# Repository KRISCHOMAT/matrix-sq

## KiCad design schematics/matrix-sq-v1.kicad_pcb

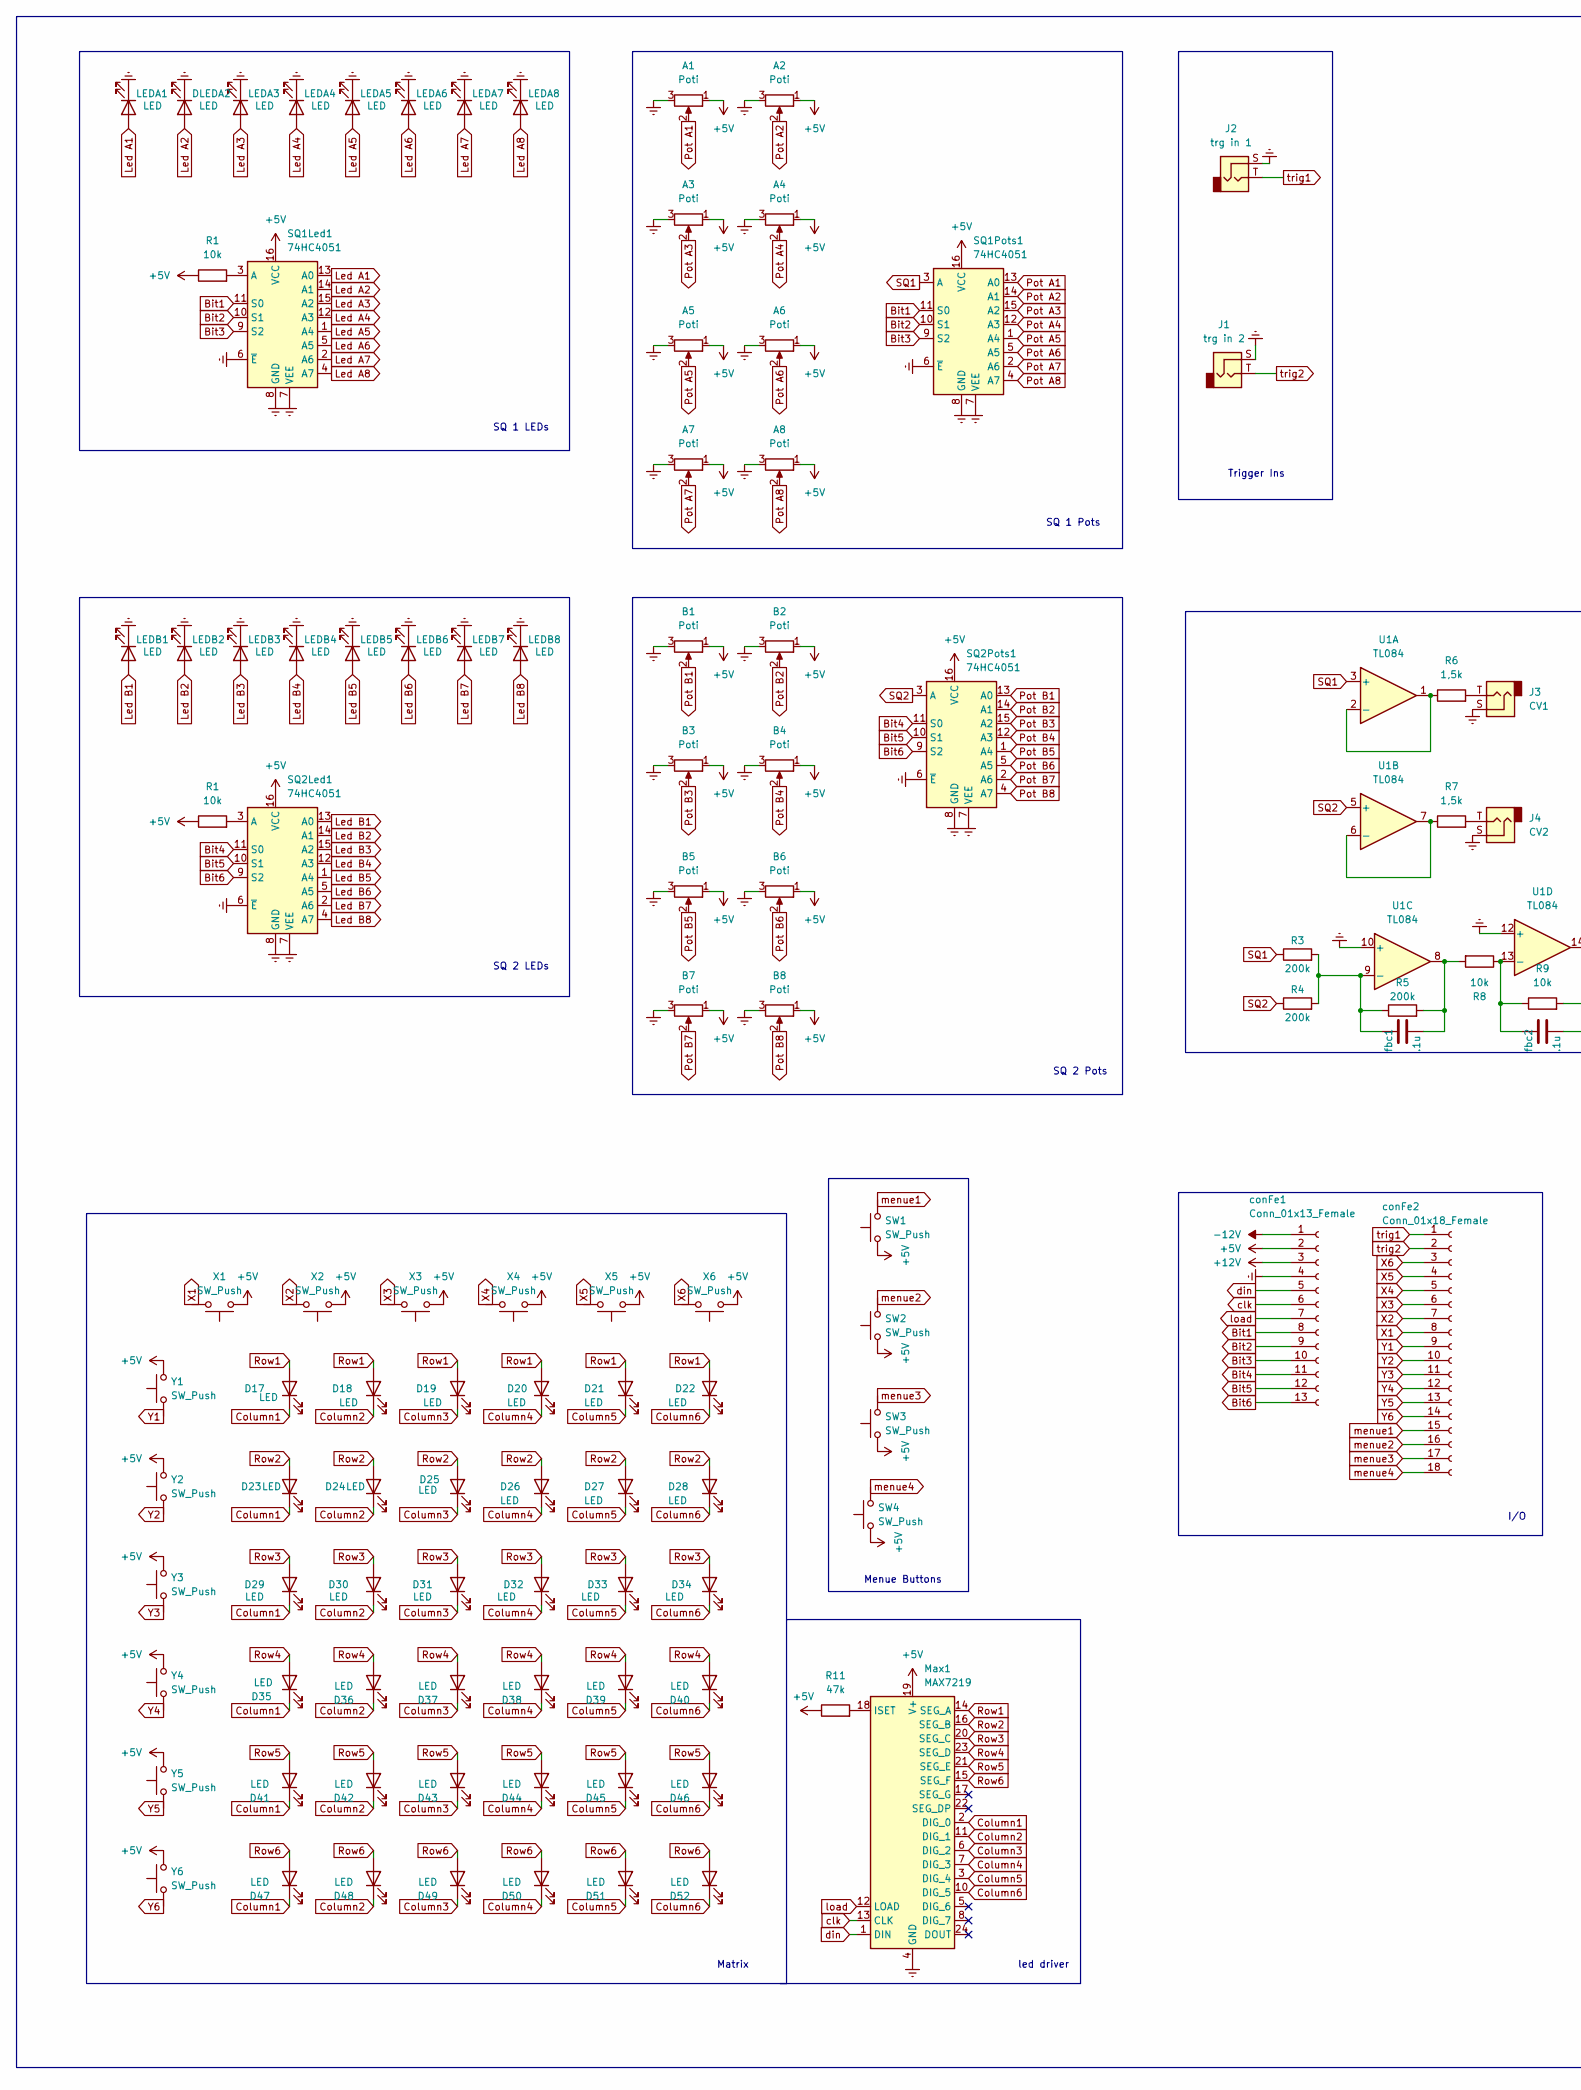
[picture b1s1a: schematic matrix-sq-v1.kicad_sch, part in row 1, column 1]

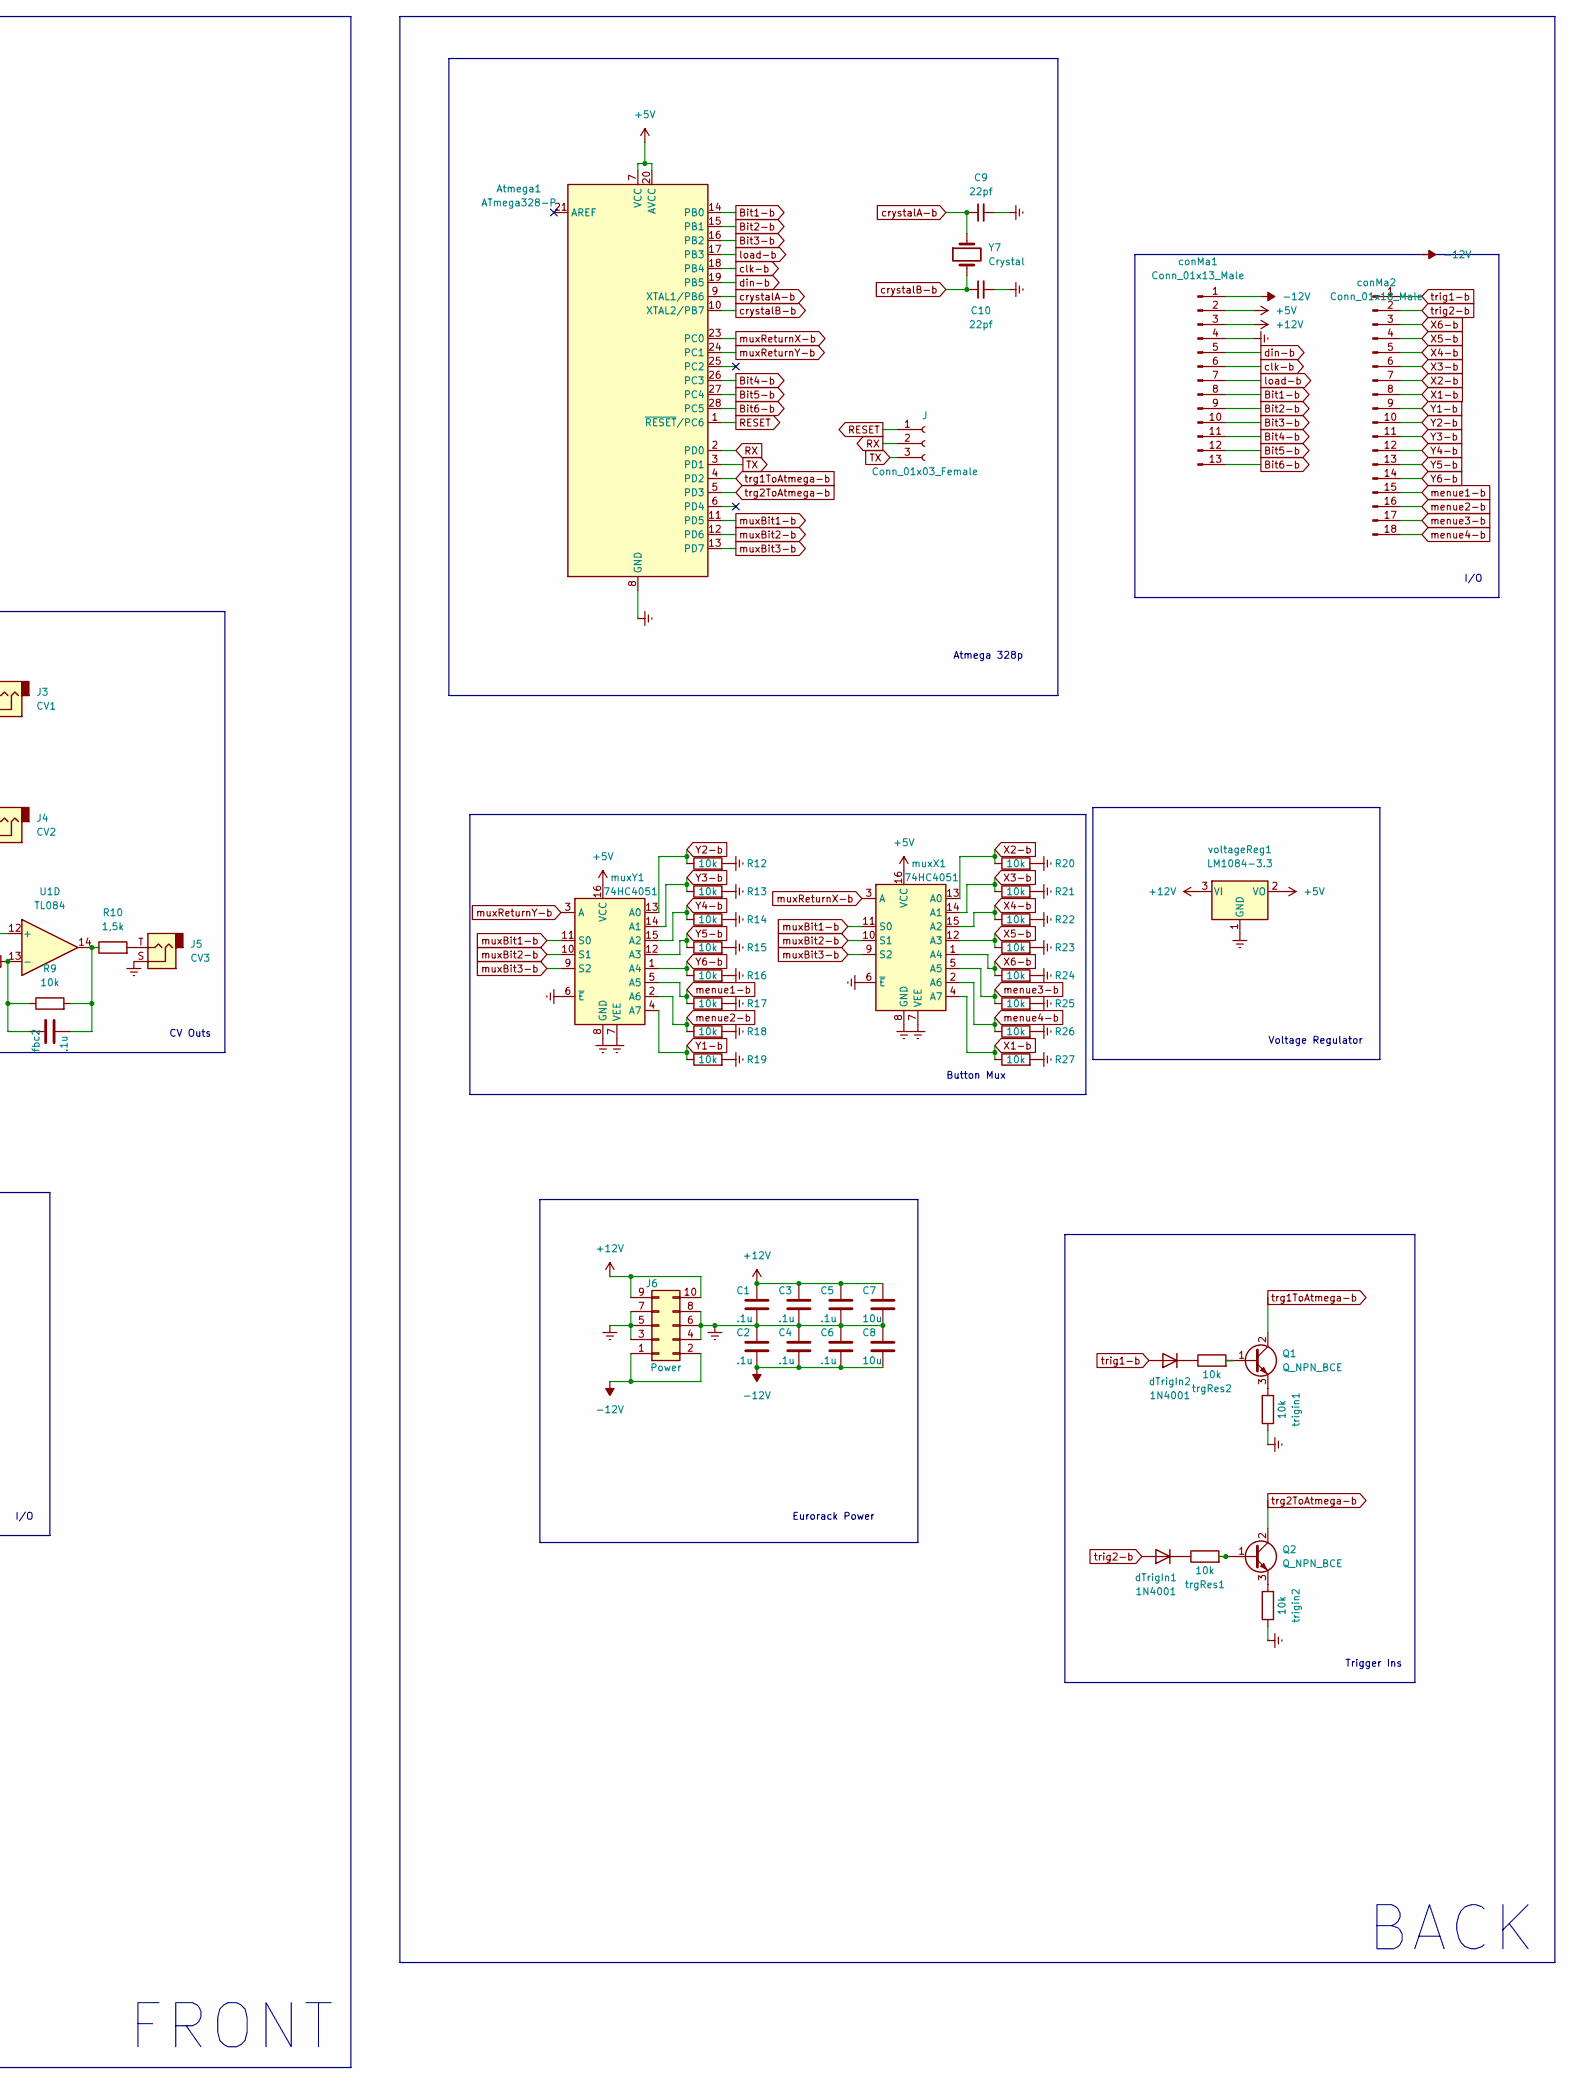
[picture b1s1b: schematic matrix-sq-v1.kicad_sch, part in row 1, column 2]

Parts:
A1, A2, A3, A4, A5, A6, A7, A8: Poti; Potentiometer_Alpha_RD901F-40-00D_Single_Vertical
Atmega1: ATmega328-P; DIP-28_W7.62mm
B1, B2, B3, B4, B5, B6, B7, B8: Poti; Potentiometer_Alpha_RD901F-40-00D_Single_Vertical
C1, C2, C3, C4, C5, C6: .1u; C_Disc_D3.0mm_W1.6mm_P2.50mm
C7, C8: 10u; C_Disc_D3.0mm_W1.6mm_P2.50mm
C9, C10: 22pf; C_Disc_D3.0mm_W1.6mm_P2.50mm
D17, D18, D19, D20, D21, D22, D23, D24, D25, D26, D27, D28, D29, D30, D31, D32, D33, D34, D35, D36, D37, D38, D39, D40, D41, D42, D43, D44, D45, D46, D47, D48, D49, D50, D51, D52: LED; LED_D3.0mm
DLEDA2: LED; LED_D3.0mm
J: Conn_01x03_Female; PinHeader_1x03_P2.54mm_Vertical
J1: trg in 2; Jack_3.5mm_QingPu_WQP-PJ398SM_Vertical_CircularHoles
J2: trg in 1; Jack_3.5mm_QingPu_WQP-PJ398SM_Vertical_CircularHoles
J3: CV1; Jack_3.5mm_QingPu_WQP-PJ398SM_Vertical_CircularHoles
J4: CV2; Jack_3.5mm_QingPu_WQP-PJ398SM_Vertical_CircularHoles
J5: CV3; Jack_3.5mm_QingPu_WQP-PJ398SM_Vertical_CircularHoles
J6: Power; PinHeader_2x05_P2.54mm_Vertical
LEDA1, LEDA3, LEDA4, LEDA5, LEDA6, LEDA7, LEDA8: LED; LED_D3.0mm
LEDB1, LEDB2, LEDB3, LEDB4, LEDB5, LEDB6, LEDB7, LEDB8: LED; LED_D3.0mm
Max1: MAX7219; DIP-24_W7.62mm
Q1, Q2: Q_NPN_BCE; TO-92Flat
R1, R12: R600; R_Axial_DIN0207_L6.3mm_D2.5mm_P7.62mm_Horizontal
R3, R4, R5: 200k; R_Axial_DIN0207_L6.3mm_D2.5mm_P7.62mm_Horizontal
R6, R7, R10: 1,5k; R_Axial_DIN0207_L6.3mm_D2.5mm_P7.62mm_Horizontal
R8, R9, R13, R14, R15, R16, R17, R18, R19, R20, R21, R22, R23, R24, R25, R26, R27: 10k; R_Axial_DIN0207_L6.3mm_D2.5mm_P7.62mm_Horizontal
R11: 47k; R_Axial_DIN0207_L6.3mm_D2.5mm_P7.62mm_Horizontal
SQ1Led1, SQ1Pots1, SQ2Led1, SQ2Pots1: 74HC4051; DIP-16_W7.62mm_Socket
SW1, SW2, SW3, SW4: SW_Push; push_button
U1: TL084; DIP-14_W7.62mm_Socket
X1, X2, X3, X4, X5, X6: SW_Push; push_button
Y1, Y2, Y3, Y4, Y5, Y6: SW_Push; push_button
Y7: Crystal; Crystal_HC18-U_Vertical
conFe1: Conn_01x13_Female; PinHeader_1x13_P2.54mm_Vertical
conFe2: Conn_01x18_Female; PinHeader_1x18_P2.54mm_Vertical
conMa1: Conn_01x13_Male; PinHeader_1x13_P2.54mm_Vertical
conMa2: Conn_01x18_Male; PinSocket_1x18_P2.54mm_Vertical
dTrigIn1, dTrigIn2: 1N4001; D_DO-41_SOD81_P10.16mm_Horizontal
fbc1, fbc2: .1u; C_Disc_D3.0mm_W1.6mm_P2.50mm
muxX1: 74HC4051; DIP-16_W7.62mm_Socket
muxY1: 74HC4051; DIP-16_W7.62mm_Socket
trgRes1, trgRes2: 10k; R_Axial_DIN0207_L6.3mm_D2.5mm_P7.62mm_Horizontal
trigin1, trigin2: 10k; R_Axial_DIN0207_L6.3mm_D2.5mm_P7.62mm_Horizontal
voltageReg1: LM1084-3.3; TO-220-3_Vertical

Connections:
+5V: A1.1, A2.1, A3.1, A4.1, A5.1, A6.1, A7.1, A8.1, Atmega1.7 (VCC), Atmega1.20 (AVCC), B1.1, B2.1, B3.1, B4.1, B5.1, B6.1, B7.1, B8.1, Max1.19 (V+), R1.1, R11.1, SQ1Led1.16 (VCC), SQ1Pots1.16 (VCC), SQ2Led1.16 (VCC), SQ2Pots1.16 (VCC), SW1.1, SW2.1, SW3.1, SW4.1, X1.1, X2.1, X3.1, X4.1, X5.1, X6.1, Y1.2, Y2.2, Y3.2, Y4.2, Y5.2, Y6.2, conFe1.2, conMa1.2, muxX1.16 (VCC), muxY1.16 (VCC), voltageReg1.2 (VO); also elsewhere on the board
+12V: C1.1, C3.1, C5.1, C7.1, J6.9, J6.10, conFe1.3, conMa1.3, voltageReg1.3 (VI)
-12V: C2.2, C4.2, C6.2, C8.2, J6.1, J6.2, conFe1.1, conMa1.1
Bit1: SQ1Led1.11 (S0), SQ1Pots1.11 (S0), conFe1.8
Bit1-b: Atmega1.14 (PB0), conMa1.8
Bit2: SQ1Led1.10 (S1), SQ1Pots1.10 (S1), conFe1.9
Bit2-b: Atmega1.15 (PB1), conMa1.9
Bit3: SQ1Led1.9 (S2), SQ1Pots1.9 (S2), conFe1.10
Bit3-b: Atmega1.16 (PB2), conMa1.10
Bit4: SQ2Led1.11 (S0), SQ2Pots1.11 (S0), conFe1.11
Bit4-b: Atmega1.26 (PC3), conMa1.11
Bit5: SQ2Led1.10 (S1), SQ2Pots1.10 (S1), conFe1.12
Bit5-b: Atmega1.27 (PC4), conMa1.12
Bit6: SQ2Led1.9 (S2), SQ2Pots1.9 (S2), conFe1.13
Bit6-b: Atmega1.28 (PC5), conMa1.13
Column1: D17.1 (K), D23.1 (K), D29.1 (K), D35.1 (K), D41.1 (K), D47.1 (K), Max1.2 (DIG_0)
Column2: D18.1 (K), D24.1 (K), D30.1 (K), D36.1 (K), D42.1 (K), D48.1 (K), Max1.11 (DIG_1)
Column3: D19.1 (K), D25.1 (K), D31.1 (K), D37.1 (K), D43.1 (K), D49.1 (K), Max1.6 (DIG_2)
Column4: D20.1 (K), D26.1 (K), D32.1 (K), D38.1 (K), D44.1 (K), D50.1 (K), Max1.7 (DIG_3)
Column5: D21.1 (K), D27.1 (K), D33.1 (K), D39.1 (K), D45.1 (K), D51.1 (K), Max1.3 (DIG_4)
Column6: D22.1 (K), D28.1 (K), D34.1 (K), D40.1 (K), D46.1 (K), D52.1 (K), Max1.10 (DIG_5)
Earth: A1.3, A2.3, A3.3, A4.3, A5.3, A6.3, A7.3, A8.3, Atmega1.8 (GND), Atmega1.22 (GND), B1.3, B2.3, B3.3, B4.3, B5.3, B6.3, B7.3, B8.3, C1.2, C2.1, C3.2, C4.1, C5.2, C6.1, C7.2, C8.1, C9.2, C10.2, DLEDA2.1 (K), J1.S, J2.S, J3.S, J4.S, J5.S, J6.3, J6.4, J6.5, J6.6, J6.7, J6.8, LEDA1.1 (K), LEDA3.1 (K), LEDA4.1 (K), LEDA5.1 (K), LEDA6.1 (K), LEDA7.1 (K), LEDA8.1 (K), LEDB1.1 (K), LEDB2.1 (K), LEDB3.1 (K), LEDB4.1 (K), LEDB5.1 (K), LEDB6.1 (K), LEDB7.1 (K), LEDB8.1 (K), Max1.4 (GND), Max1.9 (GND), R12.2, R13.2, R14.2, R15.2, R16.2, R17.2, R18.2, R19.2, R20.2, R21.2, R22.2, R23.2, R24.2, R25.2, R26.2, R27.2, SQ1Led1.6 (~E), SQ1Led1.7 (VEE), SQ1Led1.8 (GND), SQ1Pots1.6 (~E), SQ1Pots1.7 (VEE), SQ1Pots1.8 (GND), SQ2Led1.6 (~E), SQ2Led1.7 (VEE), SQ2Led1.8 (GND), SQ2Pots1.6 (~E), SQ2Pots1.7 (VEE), SQ2Pots1.8 (GND), U1.10 (+), U1.12 (+), conFe1.4, conMa1.4, muxX1.6 (~E), muxX1.7 (VEE), muxX1.8 (GND), muxY1.6 (~E), muxY1.7 (VEE), muxY1.8 (GND), trigin1.1, trigin2.1, voltageReg1.1 (GND)
Led A1: LEDA1.2 (A), SQ1Led1.13 (A0)
Led A2: DLEDA2.2 (A), SQ1Led1.14 (A1)
Led A3: LEDA3.2 (A), SQ1Led1.15 (A2)
Led A4: LEDA4.2 (A), SQ1Led1.12 (A3)
Led A5: LEDA5.2 (A), SQ1Led1.1 (A4)
Led A6: LEDA6.2 (A), SQ1Led1.5 (A5)
Led A7: LEDA7.2 (A), SQ1Led1.2 (A6)
Led A8: LEDA8.2 (A), SQ1Led1.4 (A7)
Led B1: LEDB1.2 (A), SQ2Led1.13 (A0)
Led B2: LEDB2.2 (A), SQ2Led1.14 (A1)
Led B3: LEDB3.2 (A), SQ2Led1.15 (A2)
Led B4: LEDB4.2 (A), SQ2Led1.12 (A3)
Led B5: LEDB5.2 (A), SQ2Led1.1 (A4)
Led B6: LEDB6.2 (A), SQ2Led1.5 (A5)
Led B7: LEDB7.2 (A), SQ2Led1.2 (A6)
Led B8: LEDB8.2 (A), SQ2Led1.4 (A7)
unnamed: J3.T, R6.2
unnamed: J4.T, R7.2
unnamed: J5.T, R10.2
unnamed 41: Max1.18 (ISET), R11.2; also elsewhere on the board
unnamed: Q1.1 (B), trgRes2.2
unnamed: Q1.3 (E), trigin1.2
unnamed: Q2.1 (B), trgRes1.2
unnamed: Q2.3 (E), trigin2.2
unnamed: R3.2, R4.2, R5.1, U1.9 (-), fbc1.1
unnamed: R5.2, R8.2, U1.8, fbc1.2
unnamed: R6.1, U1.1, U1.2 (-)
unnamed: R7.1, U1.6 (-), U1.7
unnamed: R8.1, R9.1, U1.13 (-), fbc2.1
unnamed: R9.2, R10.1, U1.14, fbc2.2
unnamed: dTrigIn1.1 (K), trgRes1.1
unnamed: dTrigIn2.1 (K), trgRes2.1
Pot A1: A1.2, SQ1Pots1.13 (A0)
Pot A2: A2.2, SQ1Pots1.14 (A1)
Pot A3: A3.2, SQ1Pots1.15 (A2)
Pot A4: A4.2, SQ1Pots1.12 (A3)
Pot A5: A5.2, SQ1Pots1.1 (A4)
Pot A6: A6.2, SQ1Pots1.5 (A5)
Pot A7: A7.2, SQ1Pots1.2 (A6)
Pot A8: A8.2, SQ1Pots1.4 (A7)
Pot B1: B1.2, SQ2Pots1.13 (A0)
Pot B2: B2.2, SQ2Pots1.14 (A1)
Pot B3: B3.2, SQ2Pots1.15 (A2)
Pot B4: B4.2, SQ2Pots1.12 (A3)
Pot B5: B5.2, SQ2Pots1.1 (A4)
Pot B6: B6.2, SQ2Pots1.5 (A5)
Pot B7: B7.2, SQ2Pots1.2 (A6)
Pot B8: B8.2, SQ2Pots1.4 (A7)
RESET: Atmega1.1 (~RESET/PC6), J.1
RX: Atmega1.2 (PD0), J.2
Row1: D17.2 (A), D18.2 (A), D19.2 (A), D20.2 (A), D21.2 (A), D22.2 (A), Max1.14 (SEG_A)
Row2: D23.2 (A), D24.2 (A), D25.2 (A), D26.2 (A), D27.2 (A), D28.2 (A), Max1.16 (SEG_B)
Row3: D29.2 (A), D30.2 (A), D31.2 (A), D32.2 (A), D33.2 (A), D34.2 (A), Max1.20 (SEG_C)
Row4: D35.2 (A), D36.2 (A), D37.2 (A), D38.2 (A), D39.2 (A), D40.2 (A), Max1.23 (SEG_D)
Row5: D41.2 (A), D42.2 (A), D43.2 (A), D44.2 (A), D45.2 (A), D46.2 (A), Max1.21 (SEG_E)
Row6: D47.2 (A), D48.2 (A), D49.2 (A), D50.2 (A), D51.2 (A), D52.2 (A), Max1.15 (SEG_F)
SQ1: R3.1, SQ1Pots1.3 (A), U1.3 (+)
SQ2: R4.1, SQ2Pots1.3 (A), U1.5 (+)
TX: Atmega1.3 (PD1), J.3
X1: X1.2, conFe2.8
X1-b: R27.1, conMa2.8, muxX1.4 (A7)
X2: X2.2, conFe2.7
X2-b: R20.1, conMa2.7, muxX1.13 (A0)
X3: X3.2, conFe2.6
X3-b: R21.1, conMa2.6, muxX1.14 (A1)
X4: X4.2, conFe2.5
X4-b: R22.1, conMa2.5, muxX1.15 (A2)
X5: X5.2, conFe2.4
X5-b: R23.1, conMa2.4, muxX1.12 (A3)
X6: X6.2, conFe2.3
X6-b: R24.1, conMa2.3, muxX1.1 (A4)
Y1: Y1.1, conFe2.9
Y1-b: R19.1, conMa2.9, muxY1.4 (A7)
Y2: Y2.1, conFe2.10
Y2-b: R12.1, conMa2.10, muxY1.13 (A0)
Y3: Y3.1, conFe2.11
Y3-b: R13.1, conMa2.11, muxY1.14 (A1)
Y4: Y4.1, conFe2.12
Y4-b: R14.1, conMa2.12, muxY1.15 (A2)
Y5: Y5.1, conFe2.13
Y5-b: R15.1, conMa2.13, muxY1.12 (A3)
Y6: Y6.1, conFe2.14
Y6-b: R16.1, conMa2.14, muxY1.1 (A4)
clk: Max1.13 (CLK), conFe1.6
clk-b: Atmega1.18 (PB4), conMa1.6
crystalA-b: Atmega1.9 (XTAL1/PB6), C9.1, Y7.1
crystalB-b: Atmega1.10 (XTAL2/PB7), C10.1, Y7.2
din: Max1.1 (DIN), conFe1.5
din-b: Atmega1.19 (PB5), conMa1.5
load: Max1.12 (LOAD), conFe1.7
load-b: Atmega1.17 (PB3), conMa1.7
menue1: SW1.2, conFe2.15
menue1-b: R17.1, conMa2.15, muxY1.5 (A5)
menue2: SW2.2, conFe2.16
menue2-b: R18.1, conMa2.16, muxY1.2 (A6)
menue3: SW3.2, conFe2.17
menue3-b: R25.1, conMa2.17, muxX1.5 (A5)
menue4: SW4.2, conFe2.18
menue4-b: R26.1, conMa2.18, muxX1.2 (A6)
muxBit1-b: Atmega1.11 (PD5), muxX1.11 (S0), muxY1.11 (S0)
muxBit2-b: Atmega1.12 (PD6), muxX1.10 (S1), muxY1.10 (S1)
muxBit3-b: Atmega1.13 (PD7), muxX1.9 (S2), muxY1.9 (S2)
muxReturnX-b: Atmega1.23 (PC0), muxX1.3 (A)
muxReturnY-b: Atmega1.24 (PC1), muxY1.3 (A)
trg1ToAtmega-b: Atmega1.4 (PD2), Q1.2 (C)
trg2ToAtmega-b: Atmega1.5 (PD3), Q2.2 (C)
trig1: J2.T, conFe2.1
trig1-b: conMa2.1, dTrigIn2.2 (A)
trig2: J1.T, conFe2.2
trig2-b: conMa2.2, dTrigIn1.2 (A)

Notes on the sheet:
BACK
Voltage Regulator
SQ 2 Pots
led driver
Trigger Ins
FRONT
SQ 1 Pots
Eurorack Power
SQ 2 LEDs
Matrix
Atmega 328p
Button Mux
I/O
CV Outs
Menue Buttons
SQ 1 LEDs

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
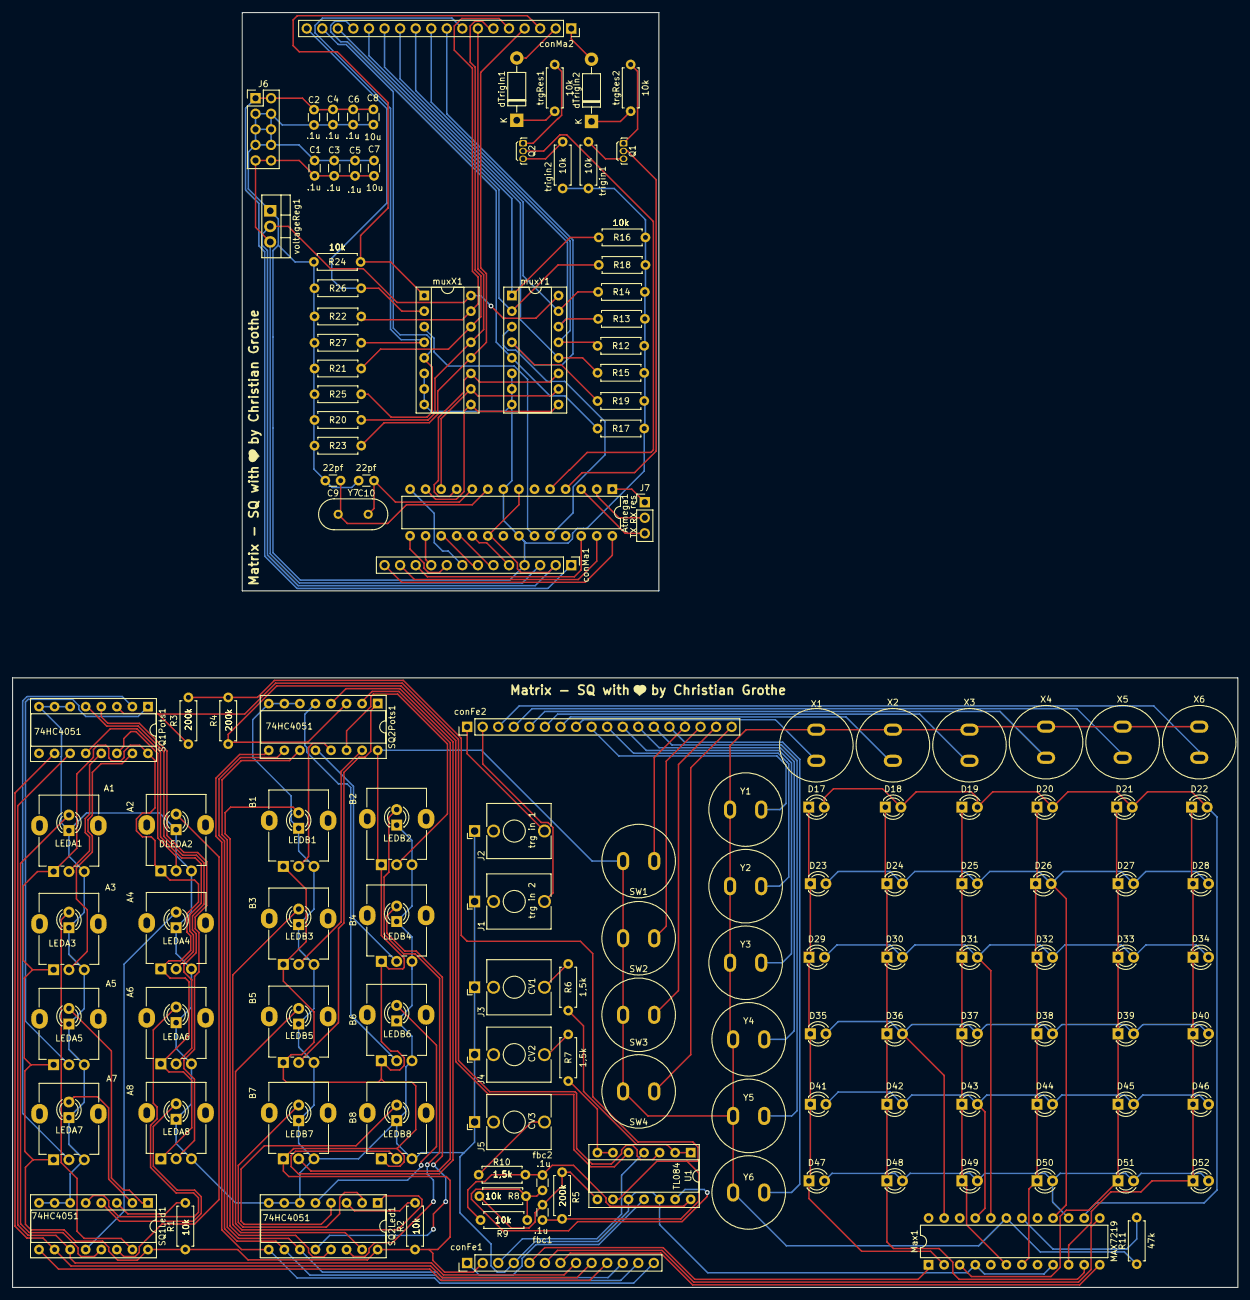
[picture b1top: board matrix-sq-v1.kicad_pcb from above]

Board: 2 copper layers, 200.0 x 208.1 mm, 153 parts (0 on the bottom side), 134 nets.

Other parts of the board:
R1#2: R600; R_Axial_DIN0207_L6.3mm_D2.5mm_P7.62mm_Horizontal
R?: 47k; R_Axial_DIN0207_L6.3mm_D2.5mm_P7.62mm_Horizontal

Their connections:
+5V: R1#2.1, R?.1; also elsewhere on the board
unnamed 41: R?.2; also elsewhere on the board

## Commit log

2022-07-04 init commit
2022-07-04 readme
2022-07-05 front PCB
2022-07-06 pcb front and fill
2022-07-06 front & backfile, gerber
2022-07-06 refactor front-gerber
2022-07-06 edge cuts
2022-07-07 new header footprints
2022-07-07 clean up
2022-07-07 cleanup
2022-08-06 refactor 6.8.
2022-08-06 renew gerber
2022-08-06 refactor
